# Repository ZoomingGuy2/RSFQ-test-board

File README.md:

# Digital RSFQ Test PCB

## Specs
- PCB designedi for I/O speeds up to 200 MHz
- 10 inputs, 20 outputs
- Compatible with CMOD A7-35T FPGA board
- 512KB SRAM
- 4MB Quad-SPI Flash
- 20,800 LUT
- 41,600 FF
- 225 KB BRAM
- 4.3W max power consumption

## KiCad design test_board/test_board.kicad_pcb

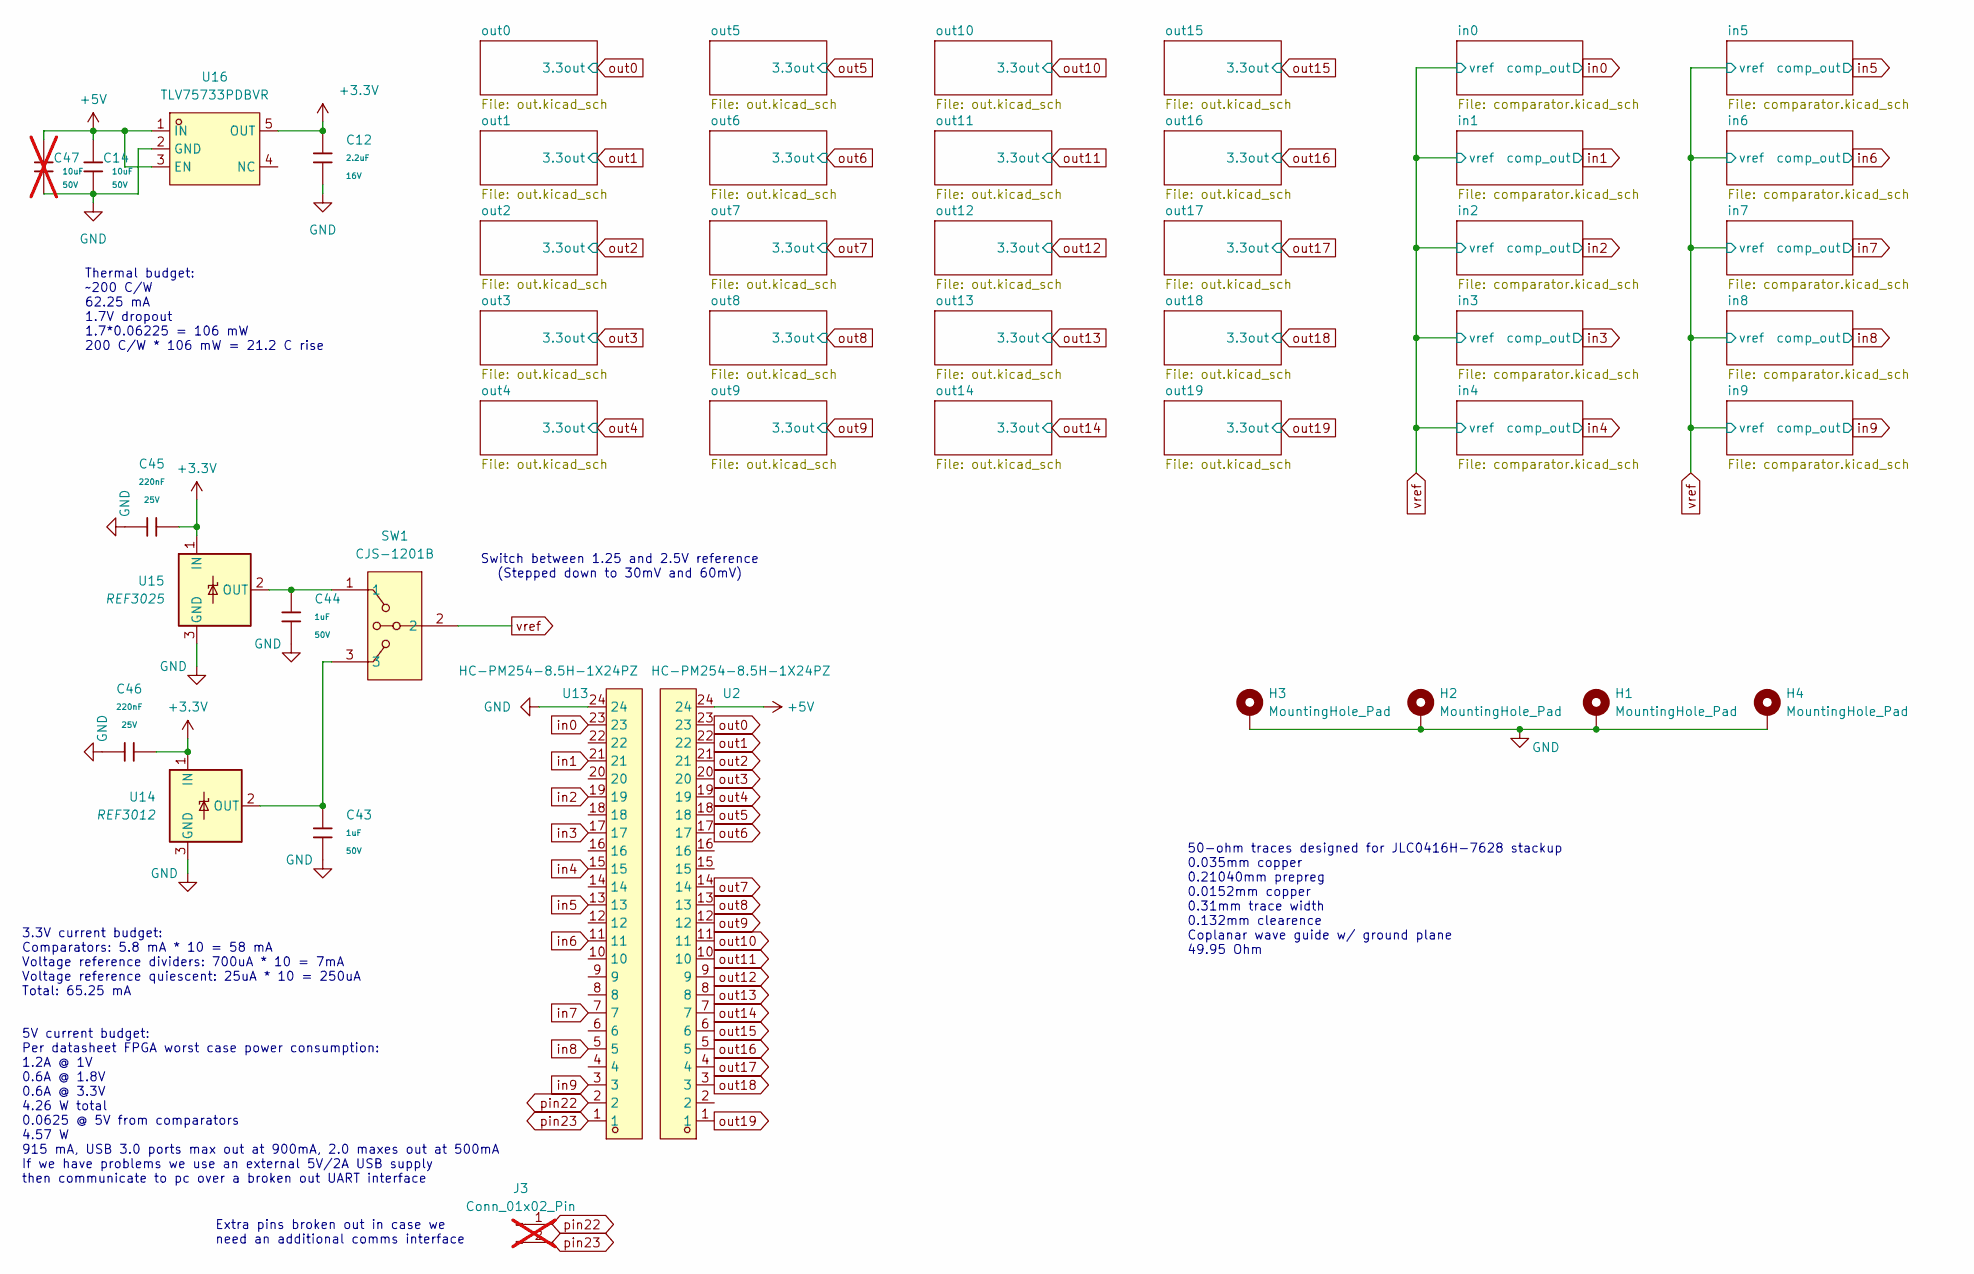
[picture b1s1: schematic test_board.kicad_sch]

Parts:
C12: 2.2uF; C_0603; Voltage Rated 16V; Tolerance ±10%; Part CL10A225KO8NNNC; LCSC C23630
C14: 10uF; C_0805; Voltage Rated 50V; Tolerance ±10%; Part GRM21BR61H106KE43L; LCSC C440198
C43, C44: 1uF; C_0603; Voltage Rated 50V; Tolerance ±10%; Part CL10A105KB8NNNC; LCSC C15849
C45, C46: 220nF; C_0603; Voltage Rated 25V; Tolerance ±10%; Part CL10B224KA8NNNC; LCSC C21120
C47: 10uF; C_0805; Voltage Rated 50V; Tolerance ±10%; Part GRM21BR61H106KE43L; LCSC C440198; not fitted
H1, H2, H3, H4: MountingHole_Pad; MountingHole_4.5mm_Pad
J3: Conn_01x02_Pin; PinHeader_1x02_P2.54mm_Vertical; not fitted
SW1: CJS-1201B; SW-SMD_CJS-1201B; LCSC Part C132858
U2, U13: HC-PM254-8.5H-1X24PZ; HDR-TH_24P-P2.54-V-F; LCSC Part C41376163
U14: REF3012; SOT-23
U15: REF3025; SOT-23
U16: TLV75733PDBVR; SOT-23-5_L2.9-W1.6-P0.95-LS2.8-BL; LCSC Part C485517

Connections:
+3.3V: C12.1, C45.2, C46.2, U14.1 (IN), U15.1 (IN), U16.5 (OUT); also elsewhere on the board
+5V: C14.1, C47.1, U2.24, U16.1 (IN), U16.3 (EN)
GND: C12.2, C14.2, C43.2, C44.2, C45.1, C46.1, C47.2, H1.1, H2.1, H3.1, H4.1, U13.24, U14.3 (GND), U15.3 (GND), U16.2 (GND); also elsewhere on the board
unnamed: C43.1, SW1.3, U14.2 (OUT)
unnamed: C44.1, SW1.1, U15.2 (OUT)
in0: U13.23; also elsewhere on the board
in1: U13.21; also elsewhere on the board
in2: U13.19; also elsewhere on the board
in3: U13.17; also elsewhere on the board
in4: U13.15; also elsewhere on the board
in5: U13.13; also elsewhere on the board
in6: U13.11; also elsewhere on the board
in7: U13.7; also elsewhere on the board
in8: U13.5; also elsewhere on the board
in9: U13.3; also elsewhere on the board
out0: U2.23; also elsewhere on the board
out1: U2.22; also elsewhere on the board
out2: U2.21; also elsewhere on the board
out3: U2.20; also elsewhere on the board
out4: U2.19; also elsewhere on the board
out5: U2.18; also elsewhere on the board
out6: U2.17; also elsewhere on the board
out7: U2.14; also elsewhere on the board
out8: U2.13; also elsewhere on the board
out9: U2.12; also elsewhere on the board
out10: U2.11; also elsewhere on the board
out11: U2.10; also elsewhere on the board
out12: U2.9; also elsewhere on the board
out13: U2.8; also elsewhere on the board
out14: U2.7; also elsewhere on the board
out15: U2.6; also elsewhere on the board
out16: U2.5; also elsewhere on the board
out17: U2.4; also elsewhere on the board
out18: U2.3; also elsewhere on the board
out19: U2.1; also elsewhere on the board
pin22: J3.1, U13.2
pin23: J3.2, U13.1
vref: SW1.2; also elsewhere on the board

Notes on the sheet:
Switch between 1.25 and 2.5V reference (Stepped down to 30mV and 60mV)
50-ohm traces designed for JLC0416H-7628 stackup 0.035mm copper 0.21040mm prepreg 0.0152mm copper 0.31mm trace width 0.132mm clearence Coplanar wave guide w/ ground plane 49.95 Ohm
Thermal budget: ~200 C/W 62.25 mA 1.7V dropout 1.7*0.06225 = 106 mW 200 C/W * 106 mW = 21.2 C rise
5V current budget: Per datasheet FPGA worst case power consumption: 1.2A @ 1V 0.6A @ 1.8V 0.6A @ 3.3V 4.26 W total 0.0625 @ 5V from comparators 4.57 W 915 mA, USB 3.0 ports max out at 900mA, 2.0 maxes out at 500mA If we have problems we use an external 5V/2A USB supply then communicate to pc over a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
3.3V current budget: Comparators: 5.8 mA * 10 = 58 mA Voltage reference dividers: 700uA * 10 = 7mA Voltage reference quiescent: 25uA * 10 = 250uA Total: 65.25 mA
Extra pins broken out in case we need an additional comms interface

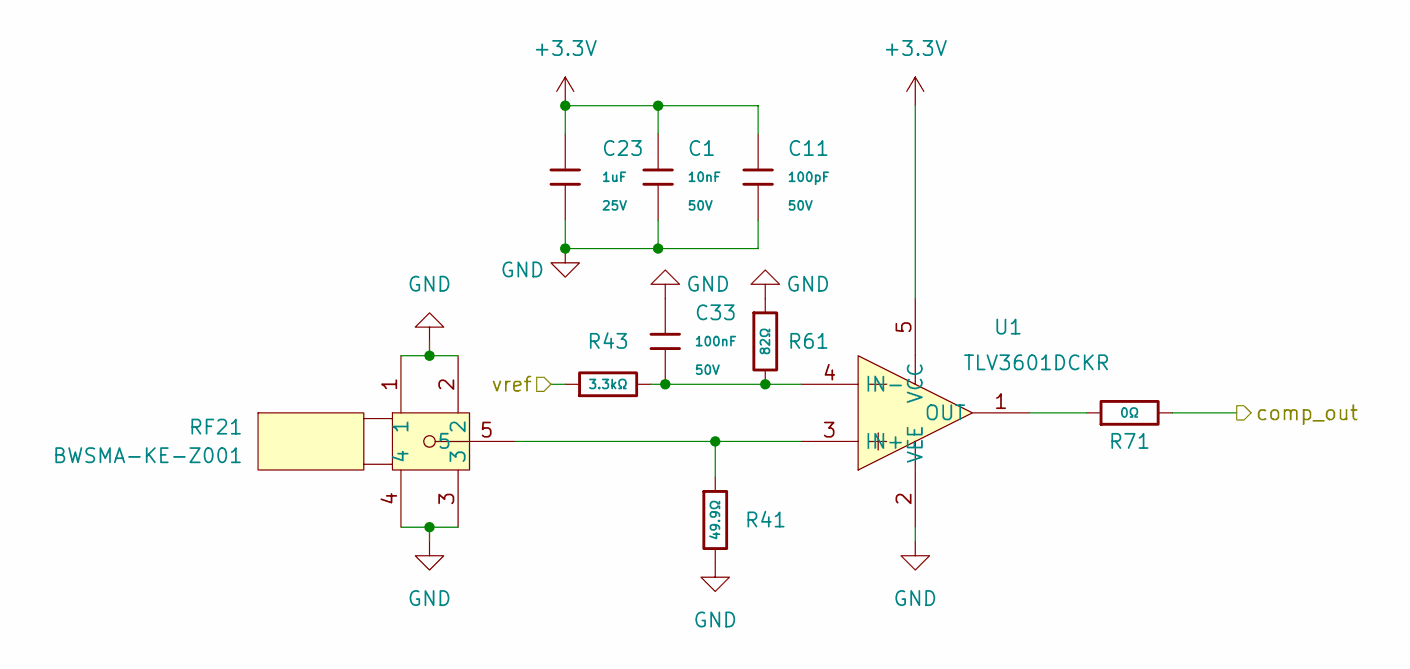
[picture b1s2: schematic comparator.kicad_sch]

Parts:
C1: 10nF; C_0402; Voltage Rated 50V; Tolerance ±10%; Part CL05B103KB5NNNC; LCSC C15195
C11: 100pF; C_0402; Voltage Rated 50V; Tolerance ±5%; Part 0402CG101J500NT; LCSC C1546
C23: 1uF; C_0402; Voltage Rated 25V; Tolerance ±10%; Part CL05A105KA5NQNC; LCSC C52923
C33: 100nF; C_0603; Voltage Rated 50V; Tolerance ±10%; Part CC0603KRX7R9BB104; LCSC C14663
R41: 49.9Ω; R_0402; Overload Voltage (Max) 50V; Tolerance ±1%; Part 0402WGF499JTCE; LCSC C25120
R43: 3.3kΩ; R_0603; Overload Voltage (Max) 75V; Tolerance ±1%; Part 0603WAF3301T5E; LCSC C22978
R61: 82Ω; R_0603; Overload Voltage (Max) 75V; Tolerance ±1%; Part 0603WAF820JT5E; LCSC C23255
R71: 0Ω; R_0402; Overload Voltage (Max) 50V; Tolerance ±1%; Part 0402WGF0000TCE; LCSC C17168
RF21: BWSMA-KE-Z001; SMA-TH_BWSMA-KE-Z001; LCSC Part C496549
U1: TLV3601DCKR; SC-70-5_L2.0-W1.3-P0.65-LS2.1-BR; LCSC Part C2974371

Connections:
+3.3V: C1.1, C11.1, C23.1, U1.5 (VCC); also elsewhere on the board
GND: C1.2, C11.2, C23.2, C33.1, R41.2, R61.1, RF21.1, RF21.2, RF21.3, RF21.4, U1.2 (VEE); also elsewhere on the board
unnamed: R41.1, RF21.5, U1.3 (IN+)
unnamed: C33.2, R43.2, R61.2, U1.4 (IN-)
unnamed: R71.1, U1.1 (OUT)
in0: R71.2; also elsewhere on the board
vref: R43.1; also elsewhere on the board

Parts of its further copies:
C2, C3, C4, C5, C6, C7, C8, C9, C10: 10nF; C_0402; Voltage Rated 50V; Tolerance ±10%; Part CL05B103KB5NNNC; LCSC C15195
C13, C15, C16, C17, C18, C19, C20, C21, C22: 100pF; C_0402; Voltage Rated 50V; Tolerance ±5%; Part 0402CG101J500NT; LCSC C1546
C24, C25, C26, C27, C28, C29, C30, C31, C32: 1uF; C_0402; Voltage Rated 25V; Tolerance ±10%; Part CL05A105KA5NQNC; LCSC C52923
C34, C35, C36, C37, C38, C39, C40, C41, C42: 100nF; C_0603; Voltage Rated 50V; Tolerance ±10%; Part CC0603KRX7R9BB104; LCSC C14663
R42, R45, R47, R49, R51, R53, R55, R57, R59: 49.9Ω; R_0402; Overload Voltage (Max) 50V; Tolerance ±1%; Part 0402WGF499JTCE; LCSC C25120
R44, R46, R48, R50, R52, R54, R56, R58, R60: 3.3kΩ; R_0603; Overload Voltage (Max) 75V; Tolerance ±1%; Part 0603WAF3301T5E; LCSC C22978
R62, R63, R64, R65, R66, R67, R68, R69, R70: 82Ω; R_0603; Overload Voltage (Max) 75V; Tolerance ±1%; Part 0603WAF820JT5E; LCSC C23255
R72, R73, R74, R75, R76, R77, R78, R79, R80: 0Ω; R_0402; Overload Voltage (Max) 50V; Tolerance ±1%; Part 0402WGF0000TCE; LCSC C17168
RF22, RF23, RF24, RF25, RF26, RF27, RF28, RF29, RF30: BWSMA-KE-Z001; SMA-TH_BWSMA-KE-Z001; LCSC Part C496549
U3, U5, U6, U7, U8, U9, U10, U11, U12: TLV3601DCKR; SC-70-5_L2.0-W1.3-P0.65-LS2.1-BR; LCSC Part C2974371

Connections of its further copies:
+3.3V: C2.1, C3.1, C4.1, C5.1, C6.1, C7.1, C8.1, C9.1, C10.1, C13.1, C15.1, C16.1, C17.1, C18.1, C19.1, C20.1, C21.1, C22.1, C24.1, C25.1, C26.1, C27.1, C28.1, C29.1, C30.1, C31.1, C32.1, U3.5 (VCC), U5.5 (VCC), U6.5 (VCC), U7.5 (VCC), U8.5 (VCC), U9.5 (VCC), U10.5 (VCC), U11.5 (VCC), U12.5 (VCC); also elsewhere on the board
GND: C2.2, C3.2, C4.2, C5.2, C6.2, C7.2, C8.2, C9.2, C10.2, C13.2, C15.2, C16.2, C17.2, C18.2, C19.2, C20.2, C21.2, C22.2, C24.2, C25.2, C26.2, C27.2, C28.2, C29.2, C30.2, C31.2, C32.2, C34.1, C35.1, C36.1, C37.1, C38.1, C39.1, C40.1, C41.1, C42.1, R42.2, R45.2, R47.2, R49.2, R51.2, R53.2, R55.2, R57.2, R59.2, R62.1, R63.1, R64.1, R65.1, R66.1, R67.1, R68.1, R69.1, R70.1, RF22.1, RF22.2, RF22.3, RF22.4, RF23.1, RF23.2, RF23.3, RF23.4, RF24.1, RF24.2, RF24.3, RF24.4, RF25.1, RF25.2, RF25.3, RF25.4, RF26.1, RF26.2, RF26.3, RF26.4, RF27.1, RF27.2, RF27.3, RF27.4, RF28.1, RF28.2, RF28.3, RF28.4, RF29.1, RF29.2, RF29.3, RF29.4, RF30.1, RF30.2, RF30.3, RF30.4, U3.2 (VEE), U5.2 (VEE), U6.2 (VEE), U7.2 (VEE), U8.2 (VEE), U9.2 (VEE), U10.2 (VEE), U11.2 (VEE), U12.2 (VEE); also elsewhere on the board
unnamed: R42.1, RF22.5, U3.3 (IN+)
unnamed: C34.2, R44.2, R62.2, U3.4 (IN-)
unnamed: R72.1, U3.1 (OUT)
unnamed: R45.1, RF23.5, U5.3 (IN+)
unnamed: C35.2, R46.2, R63.2, U5.4 (IN-)
unnamed: R73.1, U5.1 (OUT)
unnamed: R47.1, RF24.5, U6.3 (IN+)
unnamed: C36.2, R48.2, R64.2, U6.4 (IN-)
unnamed: R74.1, U6.1 (OUT)
unnamed: R49.1, RF25.5, U7.3 (IN+)
unnamed: C37.2, R50.2, R65.2, U7.4 (IN-)
unnamed: R75.1, U7.1 (OUT)
unnamed: R51.1, RF26.5, U8.3 (IN+)
unnamed: C38.2, R52.2, R66.2, U8.4 (IN-)
unnamed: R76.1, U8.1 (OUT)
unnamed: R53.1, RF27.5, U9.3 (IN+)
unnamed: C39.2, R54.2, R67.2, U9.4 (IN-)
unnamed: R77.1, U9.1 (OUT)
unnamed: R55.1, RF28.5, U10.3 (IN+)
unnamed: C40.2, R56.2, R68.2, U10.4 (IN-)
unnamed: R78.1, U10.1 (OUT)
unnamed: R57.1, RF29.5, U11.3 (IN+)
unnamed: C41.2, R58.2, R69.2, U11.4 (IN-)
unnamed: R79.1, U11.1 (OUT)
unnamed: R59.1, RF30.5, U12.3 (IN+)
unnamed: C42.2, R60.2, R70.2, U12.4 (IN-)
unnamed: R80.1, U12.1 (OUT)
in1: R72.2; also elsewhere on the board
in2: R73.2; also elsewhere on the board
in3: R74.2; also elsewhere on the board
in4: R75.2; also elsewhere on the board
in5: R76.2; also elsewhere on the board
in6: R77.2; also elsewhere on the board
in7: R78.2; also elsewhere on the board
in8: R79.2; also elsewhere on the board
in9: R80.2; also elsewhere on the board
vref: R44.1, R46.1, R48.1, R50.1, R52.1, R54.1, R56.1, R58.1, R60.1; also elsewhere on the board

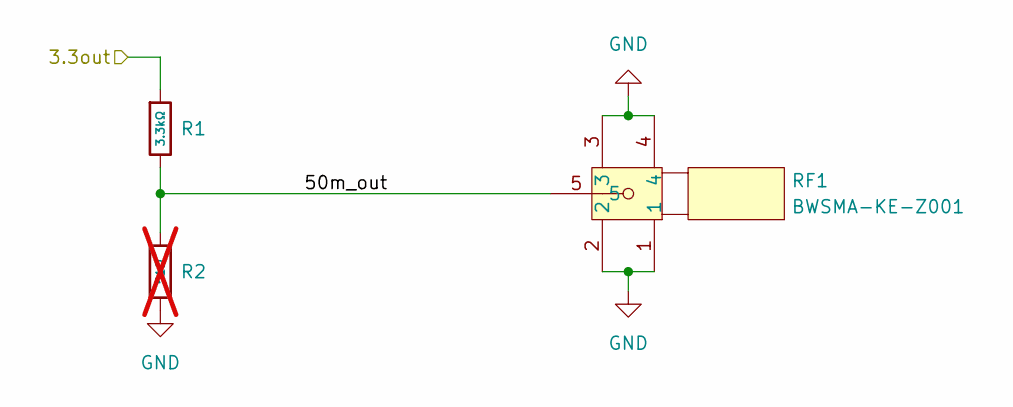
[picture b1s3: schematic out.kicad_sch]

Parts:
R1: 3.3kΩ; R_0402; Overload Voltage (Max) 50V; Tolerance ±1%; Part 0402WGF3301TCE; LCSC C25890
R2: 51Ω; R_0402; Overload Voltage (Max) 50V; Tolerance ±1%; Part 0402WGF510JTCE; LCSC C25125; not fitted
RF1: BWSMA-KE-Z001; SMA-TH_BWSMA-KE-Z001; LCSC Part C496549

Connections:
/out0/50m_out: R1.2, R2.1, RF1.5
GND: R2.2, RF1.1, RF1.2, RF1.3, RF1.4; also elsewhere on the board
out0: R1.1; also elsewhere on the board

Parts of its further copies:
R3, R5, R7, R9, R11, R13, R15, R17, R19, R21, R23, R25, R27, R29, R31, R33, R35, R37, R39: 3.3kΩ; R_0402; Overload Voltage (Max) 50V; Tolerance ±1%; Part 0402WGF3301TCE; LCSC C25890
R4, R6, R8, R10, R12, R14, R16, R18, R20, R22, R24, R26, R28, R30, R32, R34, R36, R38, R40: 51Ω; R_0402; Overload Voltage (Max) 50V; Tolerance ±1%; Part 0402WGF510JTCE; LCSC C25125; not fitted
RF2, RF3, RF4, RF5, RF6, RF7, RF8, RF9, RF10, RF11, RF12, RF13, RF14, RF15, RF16, RF17, RF18, RF19, RF20: BWSMA-KE-Z001; SMA-TH_BWSMA-KE-Z001; LCSC Part C496549

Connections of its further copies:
/out1/50m_out: R3.2, R4.1, RF2.5
/out2/50m_out: R5.2, R6.1, RF3.5
/out3/50m_out: R7.2, R8.1, RF4.5
/out4/50m_out: R9.2, R10.1, RF5.5
/out5/50m_out: R11.2, R12.1, RF6.5
/out6/50m_out: R13.2, R14.1, RF7.5
/out7/50m_out: R15.2, R16.1, RF8.5
/out8/50m_out: R17.2, R18.1, RF9.5
/out9/50m_out: R19.2, R20.1, RF10.5
/out10/50m_out: R21.2, R22.1, RF11.5
/out11/50m_out: R23.2, R24.1, RF12.5
/out12/50m_out: R25.2, R26.1, RF13.5
/out13/50m_out: R27.2, R28.1, RF14.5
/out14/50m_out: R29.2, R30.1, RF15.5
/out15/50m_out: R31.2, R32.1, RF16.5
/out16/50m_out: R33.2, R34.1, RF17.5
/out17/50m_out: R35.2, R36.1, RF18.5
/out18/50m_out: R37.2, R38.1, RF19.5
/out19/50m_out: R39.2, R40.1, RF20.5
GND: R4.2, R6.2, R8.2, R10.2, R12.2, R14.2, R16.2, R18.2, R20.2, R22.2, R24.2, R26.2, R28.2, R30.2, R32.2, R34.2, R36.2, R38.2, R40.2, RF2.1, RF2.2, RF2.3, RF2.4, RF3.1, RF3.2, RF3.3, RF3.4, RF4.1, RF4.2, RF4.3, RF4.4, RF5.1, RF5.2, RF5.3, RF5.4, RF6.1, RF6.2, RF6.3, RF6.4, RF7.1, RF7.2, RF7.3, RF7.4, RF8.1, RF8.2, RF8.3, RF8.4, RF9.1, RF9.2, RF9.3, RF9.4, RF10.1, RF10.2, RF10.3, RF10.4, RF11.1, RF11.2, RF11.3, RF11.4, RF12.1, RF12.2, RF12.3, RF12.4, RF13.1, RF13.2, RF13.3, RF13.4, RF14.1, RF14.2, RF14.3, RF14.4, RF15.1, RF15.2, RF15.3, RF15.4, RF16.1, RF16.2, RF16.3, RF16.4, RF17.1, RF17.2, RF17.3, RF17.4, RF18.1, RF18.2, RF18.3, RF18.4, RF19.1, RF19.2, RF19.3, RF19.4, RF20.1, RF20.2, RF20.3, RF20.4; also elsewhere on the board
out1: R3.1; also elsewhere on the board
out2: R5.1; also elsewhere on the board
out3: R7.1; also elsewhere on the board
out4: R9.1; also elsewhere on the board
out5: R11.1; also elsewhere on the board
out6: R13.1; also elsewhere on the board
out7: R15.1; also elsewhere on the board
out8: R17.1; also elsewhere on the board
out9: R19.1; also elsewhere on the board
out10: R21.1; also elsewhere on the board
out11: R23.1; also elsewhere on the board
out12: R25.1; also elsewhere on the board
out13: R27.1; also elsewhere on the board
out14: R29.1; also elsewhere on the board
out15: R31.1; also elsewhere on the board
out16: R33.1; also elsewhere on the board
out17: R35.1; also elsewhere on the board
out18: R37.1; also elsewhere on the board
out19: R39.1; also elsewhere on the board

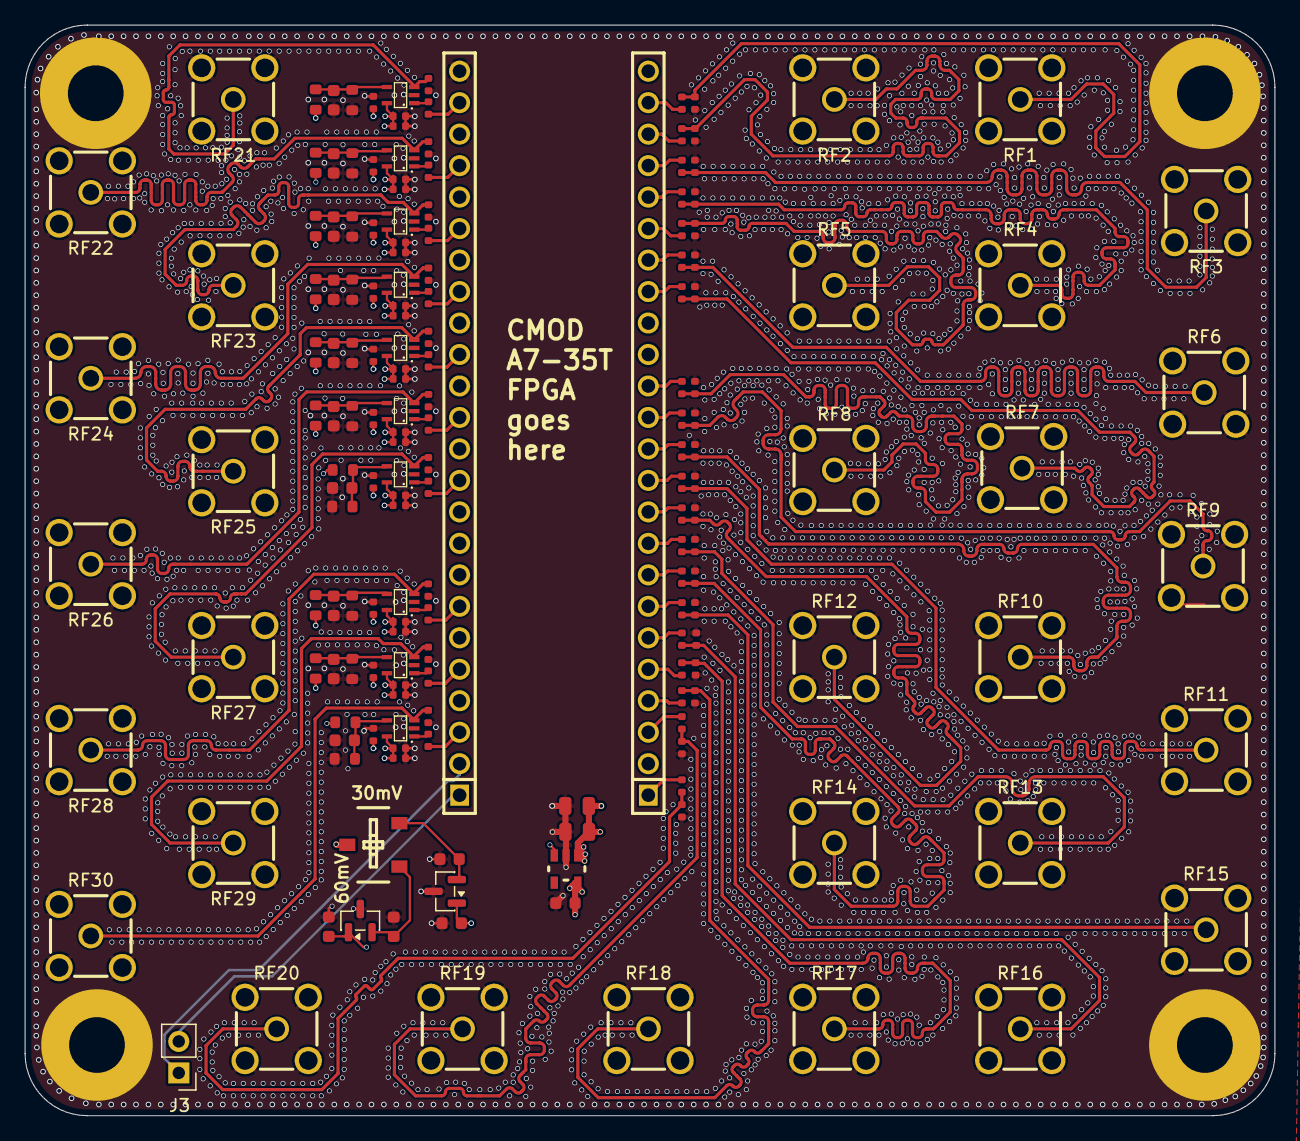
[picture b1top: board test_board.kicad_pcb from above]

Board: 4 copper layers, 100.9 x 88.0 mm, 178 parts (0 on the bottom side), 88 nets.

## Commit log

2025-12-19 added board
2025-12-19 removed old schematics
2025-12-19 added uart connector
2025-12-19 added input output count to readme
2025-12-23 added decoupling caps to regulator and changed comparator termination resistor to 49.9 ohm
2025-12-25 spaced out SMA connectors
2025-12-25 finished routing just need to add fencing vias
2025-12-25 added via fences, just need to clean them up now
2025-12-25 added modded viafence file
2025-12-27 finished board
2026-01-08 moved via fence file
2026-01-09 added pcb
2026-01-09 added 0 ohm resistor to comparator output
2026-01-09 added 0 ohm resistor
2026-01-09 fixed output
2026-01-09 changed rotation
